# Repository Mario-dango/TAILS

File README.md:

# 🦾 T.A.I.L.S. (Technical Articulated Intelligent Linkage System)

**T.A.I.L.S.** es un ecosistema integral de robótica diseñado para el control, calibración y automatización de un brazo mecánico de 3 Grados de Libertad (3-DOF).

El proyecto fusiona un diseño mecánico impreso en 3D con una electrónica dedicada basada en **STM32** y una interfaz de control de alto nivel desarrollada en **Python (PyQt5)**, permitiendo tanto el teleoperado manual como la ejecución de rutinas de aprendizaje automatizadas.

---

## 📸 Galería del Proyecto

| El Robot (T.A.I.L.S) | La Interfaz de Control |
| :---: | :---: |
|  |  |
| *Vista del ensamblaje mecánico y electrónica* | *Panel de control MVC con visualización de telemetría* |

---

## 🗂️ Arquitectura del Repositorio

El proyecto está organizado modularmente. Haz clic en cada carpeta para ver la documentación técnica detallada:

### 🖥️ [1. Interfaz Gráfica (/interfaz)](./interfaz)
El "cerebro" visual del sistema. Una aplicación de escritorio construida con **Python y PyQt5** bajo el patrón de diseño **MVC (Modelo-Vista-Controlador)**.
* **Características:** Control manual (Jogging), guardado de rutinas en JSON, visualización de sensores en tiempo real y terminal de comandos G-Code.

### ⚡ [2. Firmware (/programa)](./programa)
El código de bajo nivel que reside en el microcontrolador **STM32F103C8T6 (Bluepill)**.
* **Tecnología:** Desarrollado en **STM32CubeIDE** utilizando la librería **HAL**.
* **Funciones:** Generación de pulsos PWM para los servos, lectura de finales de carrera, interpretación de tramas seriales y control de cinemática inversa (en desarrollo).

### 🔌 [3. Diseño Electrónico (/PCB)](./PCB)
Placa de circuito impreso (PCB) personalizada para evitar el cablerío y asegurar conexiones robustas.
* **Herramienta:** Diseñado en **KiCad**.
* **Contenido:** Esquemáticos, vistas 3D de la placa, Gerbers y lista de materiales (BOM).

### 🛠️ [4. Diseño Mecánico (/diseño 3D)](./diseño%203D)
Archivos STL para la impresión 3D de la estructura.
* Incluye los diseños originales (créditos a su autor) y **modificaciones/add-ons personalizados** diseñados específicamente para el proyecto T.A.I.L.S.

### 📚 [5. Documentación (/Documentación)](./Documentación)
Recursos teóricos y técnicos adicionales.
* Datasheets de componentes.
* Informe Técnico del proyecto.
* Manuales de referencia.

---

## 🚀 Instalación y Uso Rápido

### Requisitos Previos
* Python 3.10+
* Librerías: `PyQt5`, `pyserial`

### Ejecución de la Interfaz
1. Clonar el repositorio:
   ```bash
   git clone [https://github.com/Mario-dango/TAILS.git](https://github.com/Mario-dango/TAILS.git)

2. Navegar a la carpeta de la interfaz:
    ```bash
    cd TAILS/interfaz

3. Ejecutar el punto de entrada:
    ```bash
    python main.py

## 🤝 Créditos y Autoría
* **Desarrollador Principal**: [Mario-dango](https://github.com/Mario-dango)
* **Diseño 3D Base**: [Jacklittle](https://www.thingiverse.com/thing:2520572) (ver carpeta diseño 3D para más detalles).
* **Institución**: Universidad Nacional de Cuyo.

---

Hecho con ❤️ y mucho café en Mendoza, Argentina.

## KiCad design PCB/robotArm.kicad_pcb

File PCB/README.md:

# ⚡ Diseño Electrónico y PCB - T.A.I.L.S.

Este directorio contiene todo el proyecto de diseño de hardware (Hardware Design) de la placa de control principal para el brazo robótico T.A.I.L.S. 

El diseño fue realizado íntegramente en **KiCad**, buscando crear un placa base robusta que elimine el cableado protoboard, minimice el ruido eléctrico y centralice el control de potencia y señales.

---

## 📐 Diagrama Esquemático

El cerebro de la placa es un microcontrolador **STM32F103C8T6 (Bluepill)**. El circuito está dividido en bloques funcionales para facilitar su análisis y mantenimiento:

### 🧠 Bloques Principales:
1. **Controlador STM32F103C8T6:** Se utiliza cómo nucleo crentral una placa de desarrollo bluepill con el *STM32F103C8T6* cómo microcontrolador principal.

2. **Control de Motores (Ejes X, Y, Z):** Se implementaron 3 zócalos para drivers de motores paso a paso **Pololu A4988**, incluyendo configuración de micro-pasos (MS1, MS2, MS3) y filtrado capacitivo en la alimentación de potencia.

3. **Acondicionamiento de Sensores:** Entradas para 3 finales de carrera (End-Stops). Utiliza transistores PNP (**BC558**) para adaptar y proteger las señales lógicas de 3.3V que van hacia el STM32.

4. **Gestión de Energía:** Etapa de regulación dual. A partir de la tensión de entrada principal (VCC), se extraen **5V** a través de un regulador lineal `LM7805` (para los servos y lógica general) y **3.3V** mediante un regulador ajustable `LM317` (para el STM32 y lógica de sensores).

5. **Interfaz de Usuario y Salidas:** * LEDs indicadores de estado (`HOME`, `WAIT`, `FINISH`).
   * LEDs testigos de tensión (`VCC`, `5V`, `3.3V`).

   * Salida PWM dedicada de 5V para el actuador final (Gripper / Servo).
   * Botón de Parada de Emergencia externo (E-STOP).

---

## 🛤️ Diseño de la Placa (Layout)

*(Aquí puedes colocar una captura del layout 2D de KiCad, mostrando el ruteo de las pistas)*

### Consideraciones de Diseño:
* **Planos de Masa (GND Copper Pours):** Se implementaron polígonos de masa para disipar calor y aislar el ruido de la etapa de conmutación de los motores.
* **Trazas de Potencia:** Dimensionamiento adecuado de pistas para las líneas de VCC y VMOT de los drivers A4988.

---

## 📦 Modelo 3D

*(Aquí puedes colocar un render 3D exportado directamente desde el visor 3D de KiCad)*

---

## 📋 Lista de Materiales (BOM Principal)
Se puede encontrar dentro de la carpeta [bom](./bom/ibom.html) para completar de forma interactiva y revisar todo acerca de la PCB en cuestión.

---
*Para editar o visualizar el proyecto completo, abre el archivo `.kicad_pro` en KiCad versión 8.0 o superior.*

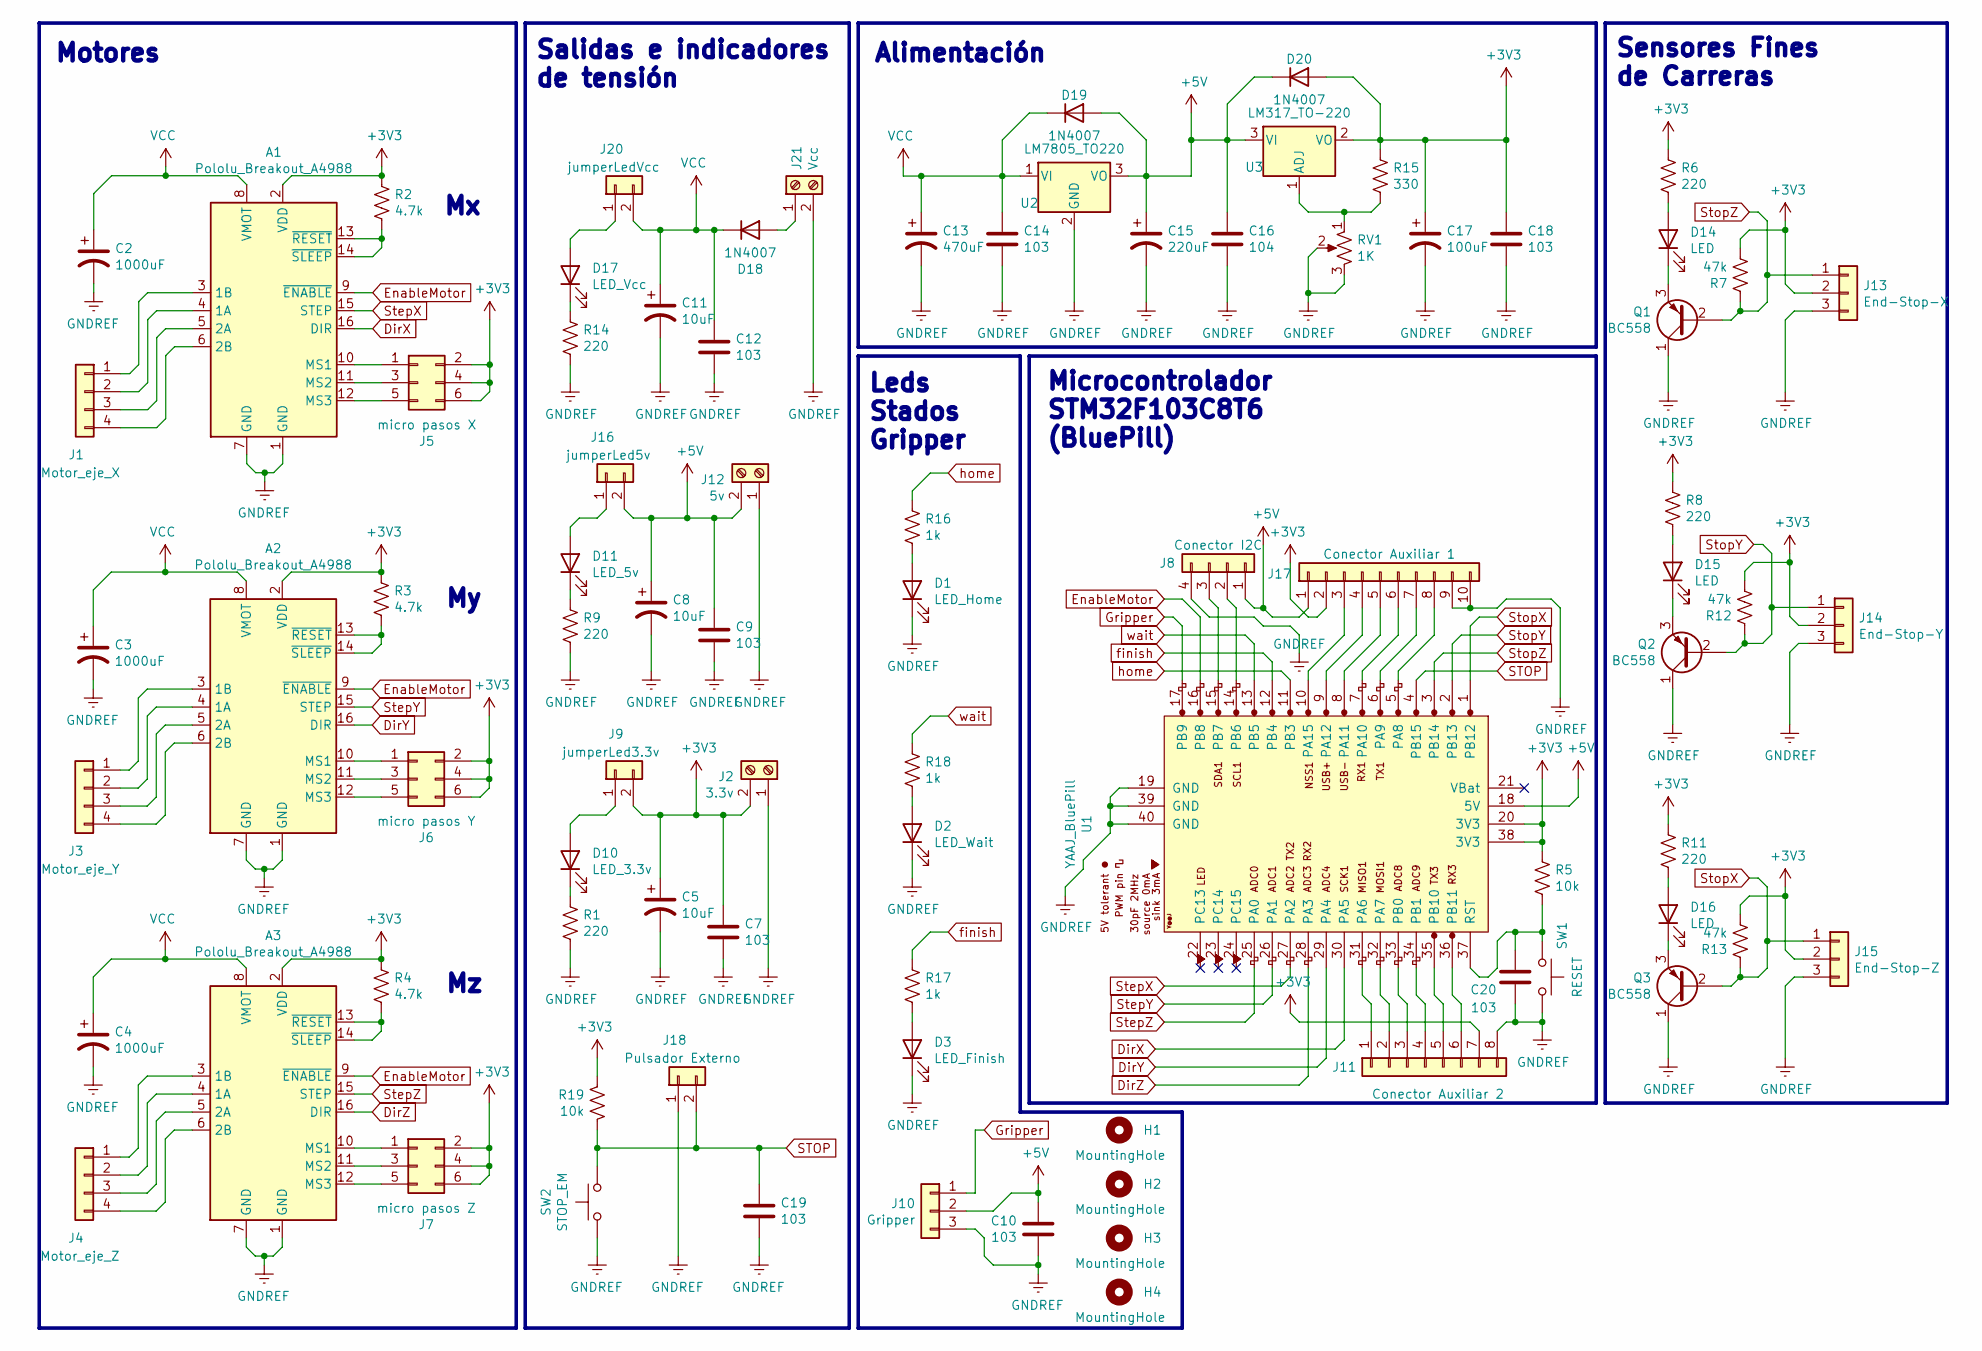
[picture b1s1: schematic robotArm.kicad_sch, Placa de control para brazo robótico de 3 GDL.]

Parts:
A1, A2, A3: Pololu_Breakout_A4988; Pololu_Breakout-16_15.2x20.3mm
C2, C3, C4: 1000uF; CP_Radial_D8.0mm_P3.80mm
C5, C8, C11: 10uF; CP_Radial_D8.0mm_P3.80mm
C7, C9, C10, C12, C14, C18, C19, C20: 103; C_Disc_D8.0mm_W2.5mm_P5.00mm
C13: 470uF; CP_Radial_D8.0mm_P3.80mm
C15: 220uF; CP_Radial_D8.0mm_P3.80mm
C16: 104; C_Disc_D8.0mm_W2.5mm_P5.00mm
C17: 100uF; CP_Radial_D8.0mm_P3.80mm
D1: LED_Home; LED_D5.0mm
D2: LED_Wait; LED_D5.0mm
D3: LED_Finish; LED_D5.0mm
D10: LED_3.3v; LED_D5.0mm
D11: LED_5v; LED_D5.0mm
D14, D15, D16: LED; LED_D5.0mm
D17: LED_Vcc; LED_D5.0mm
D18, D19, D20: 1N4007; D_DO-41_SOD81_P10.16mm_Horizontal
H1, H2, H3, H4: MountingHole; MountingHole_3.2mm_M3_DIN965
J1: Motor_eje_X; PinHeader_1x04_P2.54mm_Vertical
J2: 3.3v; TerminalBlock_Phoenix_PT-1,5-2-5.0-H_1x02_P5.00mm_Horizontal
J3: Motor_eje_Y; PinHeader_1x04_P2.54mm_Vertical
J4: Motor_eje_Z; PinHeader_1x04_P2.54mm_Vertical
J5: micro pasos X; PinHeader_2x03_P2.54mm_Vertical
J6: micro pasos Y; PinHeader_2x03_P2.54mm_Vertical
J7: micro pasos Z; PinHeader_2x03_P2.54mm_Vertical
J8: Conector I2C; PinHeader_1x04_P2.54mm_Vertical
J9: jumperLed3.3v; PinHeader_1x02_P2.54mm_Vertical
J10: Gripper; PinHeader_1x03_P2.54mm_Vertical
J11: Conector Auxiliar 2; PinHeader_1x08_P2.54mm_Vertical
J12: 5v; TerminalBlock_Phoenix_PT-1,5-2-5.0-H_1x02_P5.00mm_Horizontal
J13: End-Stop-X; PinHeader_1x03_P2.54mm_Vertical
J14: End-Stop-Y; PinHeader_1x03_P2.54mm_Vertical
J15: End-Stop-Z; PinHeader_1x03_P2.54mm_Vertical
J16: jumperLed5v; PinHeader_2x01_P2.54mm_Vertical
J17: Conector Auxiliar 1; PinSocket_1x10_P2.54mm_Vertical
J18: Pulsador Externo; PinHeader_1x02_P2.54mm_Vertical
J20: jumperLedVcc; PinHeader_2x01_P2.54mm_Vertical
J21: Vcc; TerminalBlock_Phoenix_MKDS-1,5-2_1x02_P5.00mm_Horizontal
Q1, Q2, Q3: BC558; TO-92_HandSolder
R1, R6, R8, R9, R11, R14: 220; R_Axial_DIN0207_L6.3mm_D2.5mm_P10.16mm_Horizontal
R2, R3, R4: 4.7k; R_Axial_DIN0207_L6.3mm_D2.5mm_P10.16mm_Horizontal
R5, R19: 10k; R_Axial_DIN0207_L6.3mm_D2.5mm_P10.16mm_Horizontal
R7, R12, R13: 47k; R_Axial_DIN0207_L6.3mm_D2.5mm_P10.16mm_Horizontal
R15: 330; R_Axial_DIN0207_L6.3mm_D2.5mm_P10.16mm_Horizontal
R16, R17, R18: 1k; R_Axial_DIN0207_L6.3mm_D2.5mm_P10.16mm_Horizontal
RV1: 1K; Potentiometer_Bourns_3266W_Vertical
SW1: RESET; SW_PUSH_6mm_H5mm
SW2: STOP_EM; SW_PUSH_6mm_H5mm
U1: YAAJ_BluePill; YAAJ_BluePill_1
U2: LM7805_TO220; TO-220-3_Vertical
U3: LM317_TO-220; TO-220-3_Vertical

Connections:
+3V3: A1.2 (VDD), A2.2 (VDD), A3.2 (VDD), C5.1, C7.1, C17.1, C18.1, D20.2 (A), J2.2, J5.2, J5.4, J5.6, J6.2, J6.4, J6.6, J7.2, J7.4, J7.6, J9.2, J11.7, J13.2, J14.2, J15.2, J17.2, R2.1, R3.1, R4.1, R5.1, R6.1, R7.2, R8.1, R11.1, R12.2, R13.2, R15.1, R19.1, U1.20 (3V3), U1.38 (3V3), U3.2 (VO)
+5V: C8.1, C9.1, C10.1, C15.1, C16.1, D19.2 (A), D20.1 (K), J8.1, J10.2, J12.2, J16.2, J17.1, U1.18 (5V), U2.3 (VO), U3.3 (VI)
DirX: A1.16 (DIR), U1.30 (PA5)
DirY: A2.16 (DIR), U1.29 (PA4)
DirZ: A3.16 (DIR), U1.28 (PA3)
EnableMotor: A1.9 (~ENABLE), A2.9 (~ENABLE), A3.9 (~ENABLE), U1.16 (PB8)
GNDREF: A1.1 (GND), A1.7 (GND), A2.1 (GND), A2.7 (GND), A3.1 (GND), A3.7 (GND), C2.2, C3.2, C4.2, C5.2, C7.2, C8.2, C9.2, C10.2, C11.2, C12.2, C13.2, C14.2, C15.2, C16.2, C17.2, C18.2, C19.2, C20.2, D1.1 (K), D2.1 (K), D3.1 (K), J2.1, J8.4, J10.3, J11.8, J12.1, J13.3, J14.3, J15.3, J17.9, J17.10, J18.1, J21.2, Q1.1 (C), Q2.1 (C), Q3.1 (C), R1.2, R9.2, R14.2, RV1.2, RV1.3, SW1.2, SW2.2, U1.19 (GND), U1.39 (GND), U1.40 (GND), U2.2 (GND)
Gripper: J10.1, U1.17 (PB9)
unnamed: A1.4 (1A), J1.2
unnamed: A1.3 (1B), J1.1
unnamed: A1.5 (2A), J1.3
unnamed: A1.6 (2B), J1.4
unnamed: A1.10 (MS1), J5.1
unnamed: A1.11 (MS2), J5.3
unnamed: A1.12 (MS3), J5.5
unnamed: A1.13 (~RESET), A1.14 (~SLEEP), R2.2
unnamed: A2.4 (1A), J3.2
unnamed: A2.3 (1B), J3.1
unnamed: A2.5 (2A), J3.3
unnamed: A2.6 (2B), J3.4
unnamed: A2.10 (MS1), J6.1
unnamed: A2.11 (MS2), J6.3
unnamed: A2.12 (MS3), J6.5
unnamed: A2.13 (~RESET), A2.14 (~SLEEP), R3.2
unnamed: A3.4 (1A), J4.2
unnamed: A3.3 (1B), J4.1
unnamed: A3.5 (2A), J4.3
unnamed: A3.6 (2B), J4.4
unnamed: A3.10 (MS1), J7.1
unnamed: A3.11 (MS2), J7.3
unnamed: A3.12 (MS3), J7.5
unnamed: A3.13 (~RESET), A3.14 (~SLEEP), R4.2
unnamed: D1.2 (A), R16.2
unnamed: D2.2 (A), R18.2
unnamed: D3.2 (A), R17.2
unnamed: D10.2 (A), J9.1
unnamed: D10.1 (K), R1.1
unnamed: D11.2 (A), J16.1
unnamed: D11.1 (K), R9.1
unnamed: D14.2 (A), R6.2
unnamed: D14.1 (K), Q1.3 (E)
unnamed: D15.2 (A), R8.2
unnamed: D15.1 (K), Q2.3 (E)
unnamed: D16.2 (A), R11.2
unnamed: D16.1 (K), Q3.3 (E)
unnamed: D17.2 (A), J20.1
unnamed: D17.1 (K), R14.1
unnamed: D18.2 (A), J21.1
unnamed: J8.2, U1.14 (PB6)
unnamed: J8.3, U1.15 (PB7)
unnamed: J11.1, U1.31 (PA6)
unnamed: J11.2, U1.32 (PA7)
unnamed: J11.3, U1.33 (PB0)
unnamed: J11.4, U1.34 (PB1)
unnamed: J11.5, U1.35 (PB10)
unnamed: J11.6, U1.36 (PB11)
unnamed: J17.3, U1.10 (PA15)
unnamed: J17.4, U1.9 (PA12)
unnamed: J17.5, U1.8 (PA11)
unnamed: J17.6, U1.7 (PA10)
unnamed: J17.7, U1.6 (PA9)
unnamed: J17.8, U1.5 (PA8)
unnamed: C20.1, R5.2, SW1.1, U1.37 (RST)
unnamed: R15.2, RV1.1, U3.1 (ADJ)
STOP: C19.1, J18.2, R19.2, SW2.1, U1.4 (PB15)
StepX: A1.15 (STEP), U1.27 (PA2)
StepY: A2.15 (STEP), U1.26 (PA1)
StepZ: A3.15 (STEP), U1.25 (PA0)
StopX: J15.1, Q3.2 (B), R13.1, U1.1 (PB12)
StopY: J14.1, Q2.2 (B), R12.1, U1.2 (PB13)
StopZ: J13.1, Q1.2 (B), R7.1, U1.3 (PB14)
VCC: A1.8 (VMOT), A2.8 (VMOT), A3.8 (VMOT), C2.1, C3.1, C4.1, C11.1, C12.1, C13.1, C14.1, D18.1 (K), D19.1 (K), J20.2, U2.1 (VI)
finish: R17.1, U1.12 (PB4)
home: R16.1, U1.11 (PB3)
wait: R18.1, U1.13 (PB5)

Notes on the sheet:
Salidas e indicadores de tensión
Microcontrolador STM32F103C8T6 (BluePill)
Leds Stados Gripper
Motores
Sensores Fines de Carreras
Alimentación

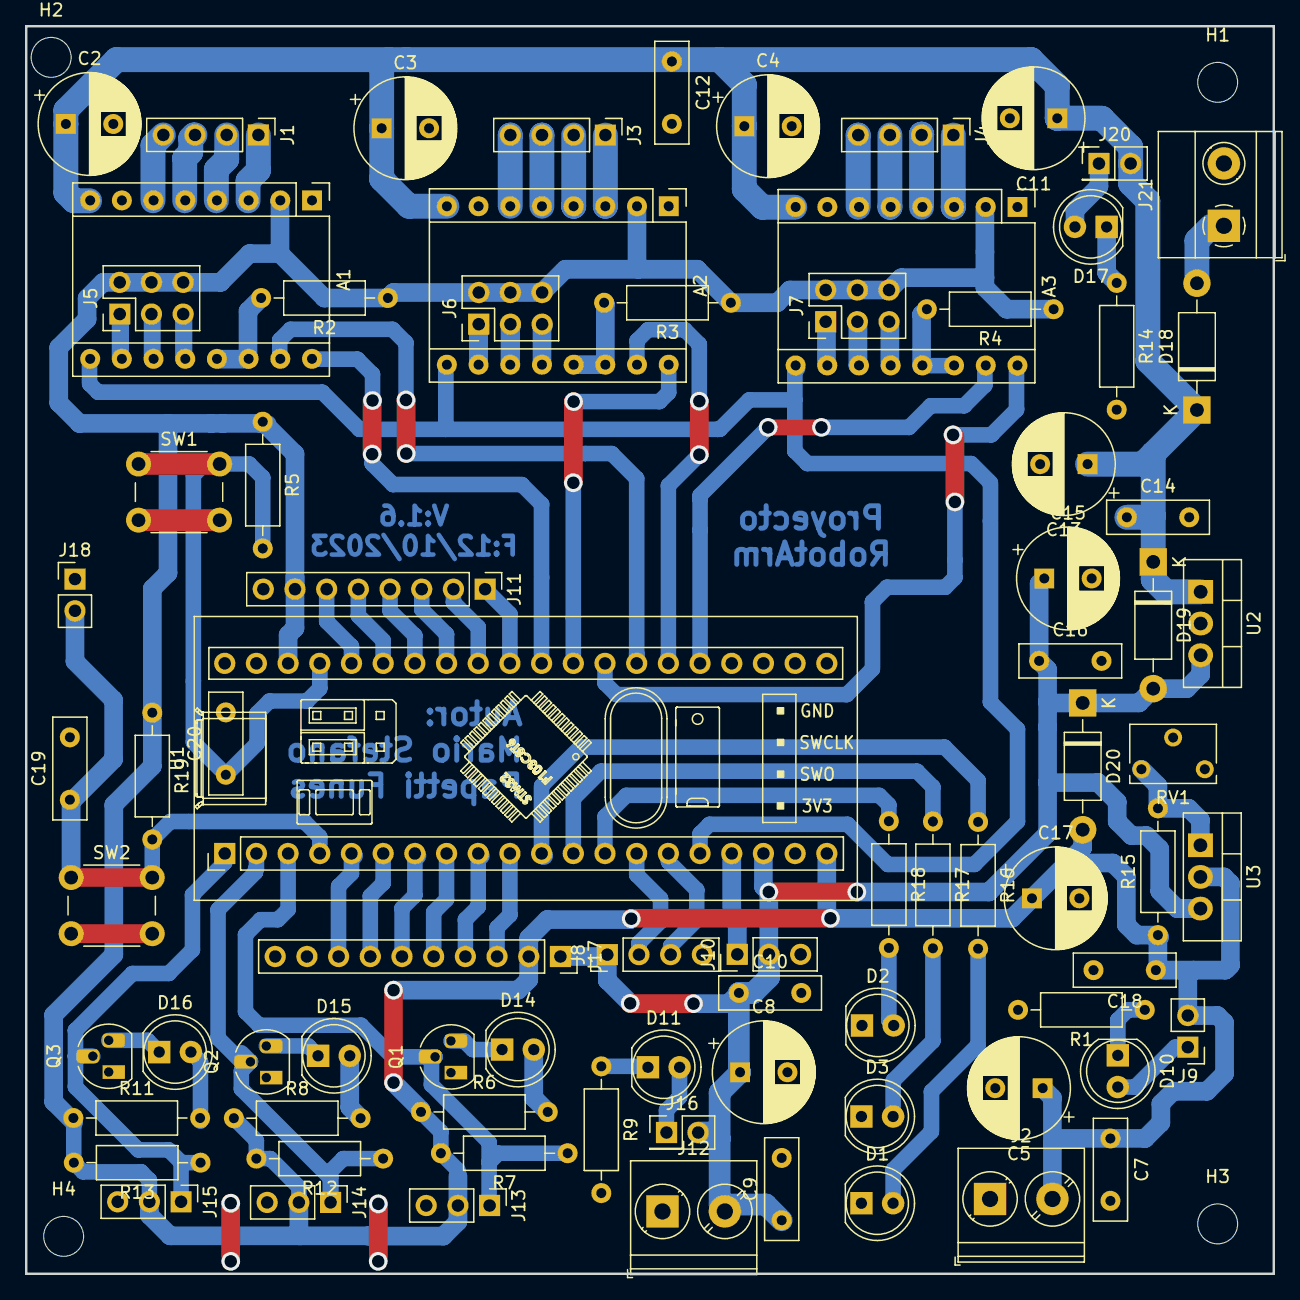
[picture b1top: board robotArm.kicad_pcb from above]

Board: 2 copper layers, 100.0 x 100.0 mm, 84 parts (0 on the bottom side), 75 nets.

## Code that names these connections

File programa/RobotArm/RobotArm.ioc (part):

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Mcu.Name=STM32F103C(8-B)Tx
Mcu.Package=LQFP48
Mcu.UserName=STM32F103C8Tx
PA0-WKUP.GPIOParameters=GPIO_Label
PA0-WKUP.GPIO_Label=StepM_Z
PA0-WKUP.Signal=GPIO_Output
PA1.GPIOParameters=GPIO_Label
PA1.GPIO_Label=StepM_Y
PA1.Signal=GPIO_Output
PA11.Mode=Device
PA11.Signal=USB_DM
PA12.Mode=Device
PA12.Signal=USB_DP
PA13.Mode=Serial_Wire
PA13.Signal=SYS_JTMS-SWDIO
PA14.Mode=Serial_Wire
PA14.Signal=SYS_JTCK-SWCLK
PA2.GPIOParameters=GPIO_Label
PA2.GPIO_Label=StepM_X
PA2.Signal=GPIO_Output
PA3.GPIOParameters=GPIO_Label
PA3.GPIO_Label=DirM_Z
PA3.Signal=GPIO_Output
PA4.GPIOParameters=GPIO_Label
PA4.GPIO_Label=DirM_Y
PA4.Signal=GPIO_Output
PA5.GPIOParameters=GPIO_Label
PA5.GPIO_Label=DirM_X
PA5.Signal=GPIO_Output
PB12.GPIOParameters=GPIO_Label
PB12.GPIO_Label=StopM_Z
PB12.Signal=GPXTI12
PB13.GPIOParameters=GPIO_Label
PB13.GPIO_Label=StopM_Y
PB13.Signal=GPXTI13
PB14.GPIOParameters=GPIO_Label
PB14.GPIO_Label=StopM_X
PB14.Signal=GPXTI14
PB15.GPIOParameters=GPIO_Label
PB15.GPIO_Label=STOP_btn
PB15.Signal=GPXTI15
PB3.GPIOParameters=GPIO_Label
PB3.GPIO_Label=Home_led
PB3.Signal=GPIO_Output
PB4.GPIOParameters=GPIO_Label
PB4.GPIO_Label=Finish_led
PB4.Signal=GPIO_Output
PB5.GPIOParameters=GPIO_Label
PB5.GPIO_Label=Wait_led
PB5.Signal=GPIO_Output
PB6.Mode=I2C
PB6.Signal=I2C1_SCL
PB7.Mode=I2C
PB7.Signal=I2C1_SDA
PB8.GPIOParameters=GPIO_Label
PB8.GPIO_Label=EnableMotors
PB8.Signal=GPIO_Output
PB9.GPIOParameters=GPIO_Label
PB9.GPIO_Label=Gripper_pin
PB9.Signal=S_TIM4_CH4
PC13-TAMPER-RTC.GPIOParameters=GPIO_Label
PC13-TAMPER-RTC.GPIO_Label=LedPcb
PC13-TAMPER-RTC.Signal=GPIO_Output
PD0-OSC_IN.Mode=HSE-External-Oscillator
PD0-OSC_IN.Signal=RCC_OSC_IN
PD1-OSC_OUT.Mode=HSE-External-Oscillator
PD1-OSC_OUT.Signal=RCC_OSC_OUT
RCC.SYSCLKFreq_VALUE=72000000
RCC.SYSCLKSource=RCC_SYSCLKSOURCE_PLLCLK
board=custom

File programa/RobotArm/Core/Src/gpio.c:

/* USER CODE BEGIN Header */
/**
  ******************************************************************************
  * @file    gpio.c
  * @brief   This file provides code for the configuration
  *          of all used GPIO pins.
  ******************************************************************************
  * @attention
  *
  * Copyright (c) 2023 STMicroelectronics.
  * All rights reserved.
  *
  * This software is licensed under terms that can be found in the LICENSE file
  * in the root directory of this software component.
  * If no LICENSE file comes with this software, it is provided AS-IS.
  *
  ******************************************************************************
  */
/* USER CODE END Header */

/* Includes ------------------------------------------------------------------*/
#include "gpio.h"

/* USER CODE BEGIN 0 */

/* USER CODE END 0 */

/*----------------------------------------------------------------------------*/
/* Configure GPIO                                                             */
/*----------------------------------------------------------------------------*/
/* USER CODE BEGIN 1 */

/* USER CODE END 1 */

/** Configure pins as
        * Analog
        * Input
        * Output
        * EVENT_OUT
        * EXTI
        * Free pins are configured automatically as Analog (this feature is enabled through
        * the Code Generation settings)
*/
void MX_GPIO_Init(void)
{

  GPIO_InitTypeDef GPIO_InitStruct = {0};

  /* GPIO Ports Clock Enable */
  __HAL_RCC_GPIOC_CLK_ENABLE();
  __HAL_RCC_GPIOD_CLK_ENABLE();
  __HAL_RCC_GPIOA_CLK_ENABLE();
  __HAL_RCC_GPIOB_CLK_ENABLE();

  /*Configure GPIO pin Output Level */
  HAL_GPIO_WritePin(LedPcb_GPIO_Port, LedPcb_Pin, GPIO_PIN_RESET);

  /*Configure GPIO pin Output Level */
  HAL_GPIO_WritePin(GPIOA, StepM_Z_Pin|StepM_Y_Pin|StepM_X_Pin|DirM_Z_Pin
                          |DirM_Y_Pin|DirM_X_Pin, GPIO_PIN_RESET);

  /*Configure GPIO pin Output Level */
  HAL_GPIO_WritePin(GPIOB, Home_led_Pin|Finish_led_Pin|Wait_led_Pin|EnableMotors_Pin, GPIO_PIN_RESET);

  /*Configure GPIO pin : PtPin */
  GPIO_InitStruct.Pin = LedPcb_Pin;
  GPIO_InitStruct.Mode = GPIO_MODE_OUTPUT_PP;
  GPIO_InitStruct.Pull = GPIO_NOPULL;
  GPIO_InitStruct.Speed = GPIO_SPEED_FREQ_LOW;
  HAL_GPIO_Init(LedPcb_GPIO_Port, &GPIO_InitStruct);

  /*Configure GPIO pins : PC14 PC15 */
  GPIO_InitStruct.Pin = GPIO_PIN_14|GPIO_PIN_15;
  GPIO_InitStruct.Mode = GPIO_MODE_ANALOG;
  HAL_GPIO_Init(GPIOC, &GPIO_InitStruct);

  /*Configure GPIO pins : PAPin PAPin PAPin PAPin
                           PAPin PAPin */
  GPIO_InitStruct.Pin = StepM_Z_Pin|StepM_Y_Pin|StepM_X_Pin|DirM_Z_Pin
                          |DirM_Y_Pin|DirM_X_Pin;
  GPIO_InitStruct.Mode = GPIO_MODE_OUTPUT_PP;
  GPIO_InitStruct.Pull = GPIO_NOPULL;
  GPIO_InitStruct.Speed = GPIO_SPEED_FREQ_LOW;
  HAL_GPIO_Init(GPIOA, &GPIO_InitStruct);

  /*Configure GPIO pins : PA6 PA7 PA8 PA9
                           PA10 PA15 */
  GPIO_InitStruct.Pin = GPIO_PIN_6|GPIO_PIN_7|GPIO_PIN_8|GPIO_PIN_9
                          |GPIO_PIN_10|GPIO_PIN_15;
  GPIO_InitStruct.Mode = GPIO_MODE_ANALOG;
  HAL_GPIO_Init(GPIOA, &GPIO_InitStruct);

  /*Configure GPIO pins : PB0 PB1 PB2 PB10
                           PB11 */
  GPIO_InitStruct.Pin = GPIO_PIN_0|GPIO_PIN_1|GPIO_PIN_2|GPIO_PIN_10
                          |GPIO_PIN_11;
  GPIO_InitStruct.Mode = GPIO_MODE_ANALOG;
  HAL_GPIO_Init(GPIOB, &GPIO_InitStruct);

  /*Configure GPIO pins : PBPin PBPin PBPin PBPin */
  GPIO_InitStruct.Pin = StopM_X_Pin|StopM_Y_Pin|StopM_Z_Pin;
  GPIO_InitStruct.Mode = GPIO_MODE_IT_FALLING;
  GPIO_InitStruct.Pull = GPIO_PULLUP;
  HAL_GPIO_Init(GPIOB, &GPIO_InitStruct);

  /*Configure GPIO pins : PBPin PBPin PBPin PBPin */
  GPIO_InitStruct.Pin = Home_led_Pin|Finish_led_Pin|Wait_led_Pin|EnableMotors_Pin;
  GPIO_InitStruct.Mode = GPIO_MODE_OUTPUT_PP;
  GPIO_InitStruct.Pull = GPIO_NOPULL;
  GPIO_InitStruct.Speed = GPIO_SPEED_FREQ_LOW;
  HAL_GPIO_Init(GPIOB, &GPIO_InitStruct);

}

/* USER CODE BEGIN 2 */

/* USER CODE END 2 */

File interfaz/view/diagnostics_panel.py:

"""
PANEL DE TEST / DIAGNÓSTICO (Ventana emergente)
Herramienta para probar el hardware pieza por pieza sin depender de una rutina
ni de la calibración: prende/apaga cada LED y mueve cada motor de forma
independiente y relativa. Ideal para verificar conexiones y cableado.

Usa los comandos de test del firmware (prefijo :*):
    :*L<H|W|F|P><0|1>      -> LED on/off
    :*M<X|Y|Z><+|-><nnn>   -> mover un motor (pasos relativos)
    :*G<A|C>               -> garra abrir/cerrar

Es autocontenido: recibe una función `send_cmd(cmd)` y cablea sus propios
botones. Los resultados de cada prueba aparecen en la consola inferior.
"""

from PyQt5.QtWidgets import (QDialog, QWidget, QVBoxLayout, QHBoxLayout, QGridLayout,
                             QGroupBox, QPushButton, QLabel, QSpinBox, QCheckBox,
                             QScrollArea, QFrame, QApplication)
from PyQt5.QtCore import Qt


class DiagnosticsPanel(QDialog):
    def __init__(self, send_cmd, parent=None):
        super().__init__(parent)
        self.send_cmd = send_cmd  # callable: envía un comando al robot

        self.setWindowTitle("Panel de Test / Diagnóstico — T.A.I.L.S.")

        # Windows le agrega a todo QDialog un botón "?" (ayuda contextual) en la
        # barra de título. Acá no hay ayuda contextual que mostrar, así que el
        # botón no hacía absolutamente nada: lo sacamos.
        self.setWindowFlags(self.windowFlags() & ~Qt.WindowContextHelpButtonHint)

        # El contenido va dentro de un área desplazable y la ventana se mide
        # contra la PANTALLA, no contra un alto fijo: con 660px fijos, en un
        # monitor chico (o con escalado de Windows al 125%) la ventana salía por
        # abajo y los últimos controles quedaban fuera del alcance del mouse.
        disponible = QApplication.primaryScreen().availableGeometry().height()
        self.resize(560, min(680, max(360, disponible - 80)))
        self.setMinimumSize(460, 360)

        marco = QVBoxLayout(self)
        marco.setContentsMargins(0, 0, 0, 0)

        scroll = QScrollArea()
        scroll.setWidgetResizable(True)
        scroll.setFrameShape(QFrame.NoFrame)
        scroll.setHorizontalScrollBarPolicy(Qt.ScrollBarAlwaysOff)
        marco.addWidget(scroll)

        contenido = QWidget()
        scroll.setWidget(contenido)
        layout = QVBoxLayout(contenido)

        # --- GUÍA RÁPIDA ---
        guia = QLabel(
            "<b>Guía rápida</b><br>"
            "Probá el hardware de a una parte por vez.<br>"
            "• <b>LEDs:</b> ON/OFF para verificar cada indicador de la placa.<br>"
            "• <b>Motores:</b> elegí los pasos y movés cada eje con + / − "
            "(movimiento relativo, no necesita Home).<br>"
            "• <b>Garra:</b> abrir/cerrar el servo.<br>"
            "<i>Ojo:</i> requiere estar conectado y NO estar en Paro de Emergencia. "
            "Cada resultado se ve en la consola inferior."
        )
        guia.setWordWrap(True)
        guia.setStyleSheet("background-color:#20232a; color:#ddd; padding:8px; border-radius:6px;")
        layout.addWidget(guia)

        # --- LEDS ---
        grp_led = QGroupBox("LEDs (prender / apagar)")
        gl = QGridLayout(grp_led)
        leds = [("Home", "H"), ("Wait / Busy", "W"), ("Finish", "F"), ("LED Placa (PC13)", "P")]
        for row, (name, code) in enumerate(leds):
            gl.addWidget(QLabel(name), row, 0)
            b_on = QPushButton("ON")
            b_on.setStyleSheet("background-color:#2e7d32; color:white; font-weight:bold;")
            b_on.clicked.connect(lambda _=False, c=code: self.send_cmd(f":*L{c}1"))
            b_off = QPushButton("OFF")
            b_off.clicked.connect(lambda _=False, c=code: self.send_cmd(f":*L{c}0"))
            gl.addWidget(b_on, row, 1)
            gl.addWidget(b_off, row, 2)
        layout.addWidget(grp_led)

        # --- MOTORES ---
        grp_mot = QGroupBox("Motores (movimiento relativo independiente)")
        gm = QGridLayout(grp_mot)

        gm.addWidget(QLabel("Pasos por pulsación:"), 0, 0)
        self.spin_steps = QSpinBox()
        self.spin_steps.setRange(1, 9999)
        self.spin_steps.setValue(100)
        gm.addWidget(self.spin_steps, 0, 1, 1, 2)

        for row, axis in enumerate(["X", "Y", "Z"], start=1):
            gm.addWidget(QLabel(f"Eje {axis}"), row, 0)
            b_minus = QPushButton(f"{axis} −")
            b_minus.setMinimumHeight(40)
            b_minus.clicked.connect(lambda _=False, a=axis: self.jog(a, '-'))
            b_plus = QPushButton(f"{axis} +")
            b_plus.setMinimumHeight(40)
            b_plus.clicked.connect(lambda _=False, a=axis: self.jog(a, '+'))
            gm.addWidget(b_minus, row, 1)
            gm.addWidget(b_plus, row, 2)
        layout.addWidget(grp_mot)

        # --- GARRA + ENABLE ---
        grp_extra = QGroupBox("Garra y Torque")
        ge = QHBoxLayout(grp_extra)
        b_open = QPushButton("Garra Abrir")
        b_open.clicked.connect(lambda: self.send_cmd(":*GA"))
        b_close = QPushButton("Garra Cerrar")
        b_close.clicked.connect(lambda: self.send_cmd(":*GC"))
        self.chk_enable = QCheckBox("Torque motores (Enable)")
        self.chk_enable.setChecked(True)
        self.chk_enable.toggled.connect(lambda on: self.send_cmd(":-E1" if on else ":-E0"))
        ge.addWidget(b_open)
        ge.addWidget(b_close)
        ge.addWidget(self.chk_enable)
        layout.addWidget(grp_extra)

        layout.addStretch()
        nota = QLabel("<i>Los resultados de cada prueba aparecen en la consola inferior.</i>")
        nota.setWordWrap(True)
        layout.addWidget(nota)

    def jog(self, axis, sign):
        """Envía un movimiento relativo de prueba al eje indicado."""
        steps = self.spin_steps.value()
        self.send_cmd(f":*M{axis}{sign}{steps:03d}")

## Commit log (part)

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2026-01-05 El homming funciona!
2026-01-05 modo ejecución v1.0 funciona correctamente
2026-01-05 Se avanzo interfaz 3 modos funcionales v1.0
2026-01-19 actualizaciones en la interfaz
2026-01-19 solucion de puerto com
2026-01-19 reparacion del com.2
2026-01-20 Recuperando cambios del stash
2026-01-20 Se recuperaron las modificaciones de interfaz
2026-01-20 readme de stm32
2026-01-20 Se agregó leds en interfaz, botón de limpiar aprendizaje, se arregló configuración de velocidad en bluepill
2026-01-20 se arreglaron los handles de botones para no interactuar cuando el robot off
2026-01-20 Interfaz (#7)
    * actualizaciones en la interfaz
    * solucion de puerto com
    * reparacion del com.2
    * Recuperando cambios del stash
    * Se recuperaron las modificaciones de interfaz
    * readme de stm32
2026-01-20 Interfaz (#9)
    * actualizaciones en la interfaz
    * solucion de puerto com
    * reparacion del com.2
    * Recuperando cambios del stash
    * Se recuperaron las modificaciones de interfaz
    * readme de stm32
2026-01-20 Revise README.md for project structure and features
    Updated project documentation for clarity and detail.
2026-01-21 Se actualizo interfaz v1.0
2026-01-21 Se agregó rampa de velocidad
2026-01-21 PCB pull from master (#12)
    * Update README.md
    Se agregó descripción, introducción y fuentes.
    * Se consiguió una primera versión de Eje-Stop funcional
    * Se inició una interfaz en python sencilla para la comunicación con el robot
    * Se comenzó con conexión USB
    * Se agregó LCD i2c y lógica de CDC
2026-01-21 PCB pull from master (#12) (#13)
    * Update README.md
    Se agregó descripción, introducción y fuentes.
    * Se consiguió una primera versión de Eje-Stop funcional
    * Se inició una interfaz en python sencilla para la comunicación con el robot
    * Se comenzó con conexión USB
    * Se agregó LCD i2c y lógica de CDC
2026-02-22 Se agregaron iconos kawaii
2026-02-23 Se factorizaron view.py, controller.py. Agregaron README's y orden de carpetas
2026-02-23 Fix: Limpieza de caché y actualización de gitignore
2026-02-23 Fix: pruebas unitarias funcionales
2026-02-23 Limpieza: Eliminación de archivos temporales de KiCad
2026-03-10 se agregaron imagenes y actualizaron algunos readmes

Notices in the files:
README.md:
License: MIT
